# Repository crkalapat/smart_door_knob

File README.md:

# Smart Door Knob

*A Matter compatible smart door knob*

## Overview
This smart door knob is designed specifically for Kwikset bed/room door knobs. The door knob is compatible with the [Matter](https://en.wikipedia.org/wiki/Matter_(standard)) smart home protocol, so it works with Amazon Alexa, Apple HomeKit, and Google Home. The only requirement is that you have a [Thread Border Router](https://www.matteralpha.com/explainer/thread-border-router) for the microcontroller (Arduino Nano Matter) to connect to.

## Instructions
After the code is flashed, you will need to set it up. You can use the QR Code link provided in the terminal, or use a manual pairing code. Once paired, (and whenever it turns on/resets after that) the RGB LED will begin to pulse blue. This signifies that it is in the process of connecting to the Thread Border Router that you specificed.

Once connected, the LED will turn off, indicating that the process has finished and that the door lock is ready to be controlled. You can then freely control the door lock either through your Matter smart home, or manually with the buttons. When the door is locked, the LED will be red, and when unlocked, the LED will be green. To unlock the door manually, enter the passcode specified in the code under the `buffer` variable (1-1-3-2 by default) using the corresponding buttons 1, 2, or 3. To lock the door manually, simply press any combination of incorrect buttons, and the door will lock if it wasn't locked already.

If you hit a wrong button and want to clear your input, simply wait for 5 seconds and all button input will be erased. If this is too long, the `inputWaitTime` variable can be customized in the code to change the clear time.

## Firmware Installation
Open the repo folder in Arduino IDE. If needed, pin numbers for components such as the RGB LED, servo, and buttons can be changed manually in the Arduino code file. Flash the code onto the Arduino Nano Matter. Once done, in the Serial Monitor (115200 baud), information for pairing the door lock can be found and used with a Matter compatible device.

## BOM
- 1x [Arduino Nano Matter with headers](https://store-usa.arduino.cc/collections/internet-of-things/products/nano-matter) (or [similar board](https://github.com/SiliconLabs/arduino/blob/main/readme.md))

- 2x 1x15 Socket Headers

- 1x [MG90 Servo](https://www.amazon.com/MG90S-Servo-Motor-Helicopter-Arduino/dp/B07L6FZVT1?crid=VYZSRM9027BT) (SG90 also works)

- 3x [6mm Push Buttons](https://www.amazon.com/DAOKI-Miniature-Momentary-Tactile-Quality/dp/B01CGMP9GY?crid=3P0EFZBRL88C4&)

- 1x [Micro USB Connector](https://www.mouser.com/ProductDetail/Amphenol-FCI/10118194-0011LF?qs=9lcNTSmDlCqQOdqcAswPOg%3D%3D)

- 1x [RGB LED](https://www.amazon.com/EDGELEC-Tri-Color-Multicolor-Diffused-Resistors/dp/B077XGF3YR?crid=3S7KMO6E8I0PC)

- 1x [PCB Board](pcb/)

- 8x M3x12mm screws

- 7x [Custom 3D-printed parts](cad/printed)

- 6x M3 nuts

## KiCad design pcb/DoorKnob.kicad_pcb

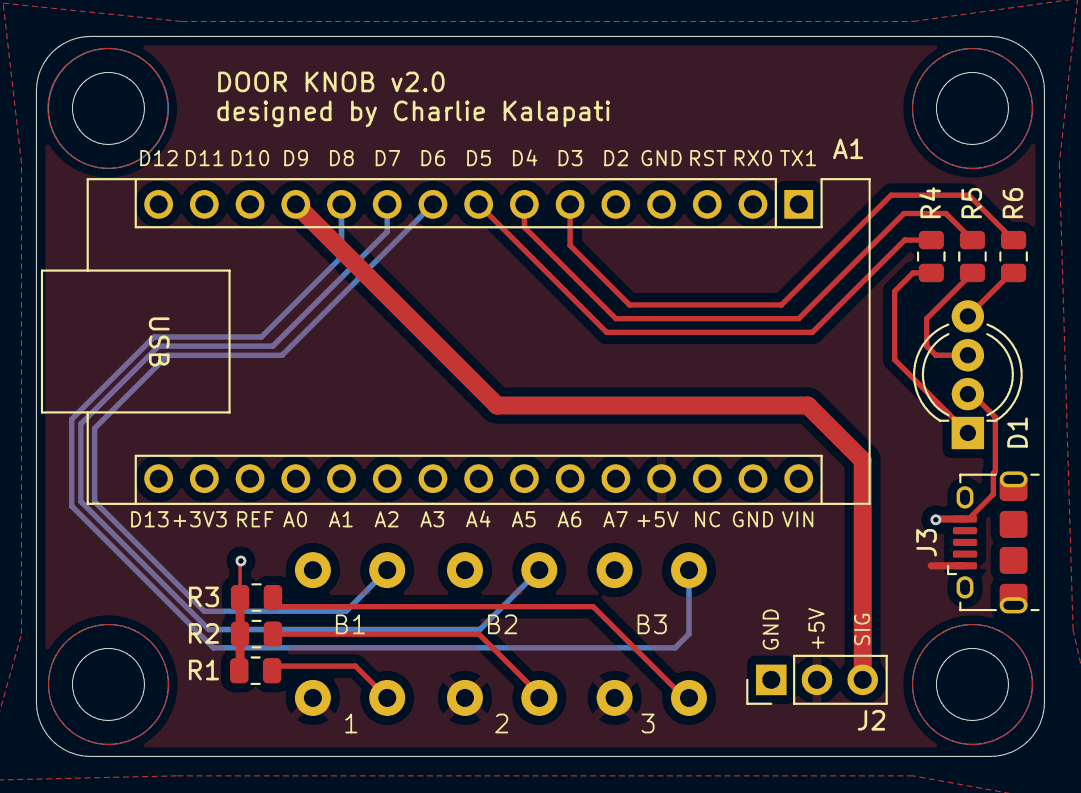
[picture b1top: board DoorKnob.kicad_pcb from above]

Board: 2 copper layers, 56.0 x 40.0 mm, 13 parts (0 on the bottom side), 15 nets.

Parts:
A1: Arduino_Nano_Matter; Arduino_Nano
B1, B2, B3: Button_6mm
D1: LED_RKGB; LED_D5.0mm-4_RGB_Wide_Pins
J2: Conn_01x03; PinHeader_1x03_P2.54mm_Vertical
J3: USB_B_Micro; USB_Micro-B_Amphenol_10118194-0001LF_Horizontal
R1, R2, R3, R4, R5, R6: 220R; R_0805_2012Metric

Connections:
+5V: A1.27 (+5V), B1.3, B2.3, B3.3, J2.2, J3.1 (VBUS)
GND: A1.29 (GND), D1.2 (K), J2.1, J3.5 (GND), R1.2, R2.2, R3.2
unnamed: A1.6 (D3), R6.1
unnamed: A1.7 (D4), R5.1
unnamed: A1.8 (D5), R4.1
unnamed: A1.9 (D6), B1.2
unnamed: A1.10 (D7), B2.2
unnamed: A1.11 (D8), B3.2
unnamed: A1.12 (D9), J2.3
unnamed: B1.4, R1.1
unnamed: B2.4, R2.1
unnamed: B3.4, R3.1
unnamed: D1.4 (BA), R6.2
unnamed: D1.3 (GA), R5.2
unnamed: D1.1 (RA), R4.2

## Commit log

2025-01-08 Update README, add code and gitignore
2025-01-08 Rename ino file, update commenting so code is clearer
2025-06-11 Update README, add images and CAD
2025-06-11 Add PCB files
2025-06-11 Fix README
